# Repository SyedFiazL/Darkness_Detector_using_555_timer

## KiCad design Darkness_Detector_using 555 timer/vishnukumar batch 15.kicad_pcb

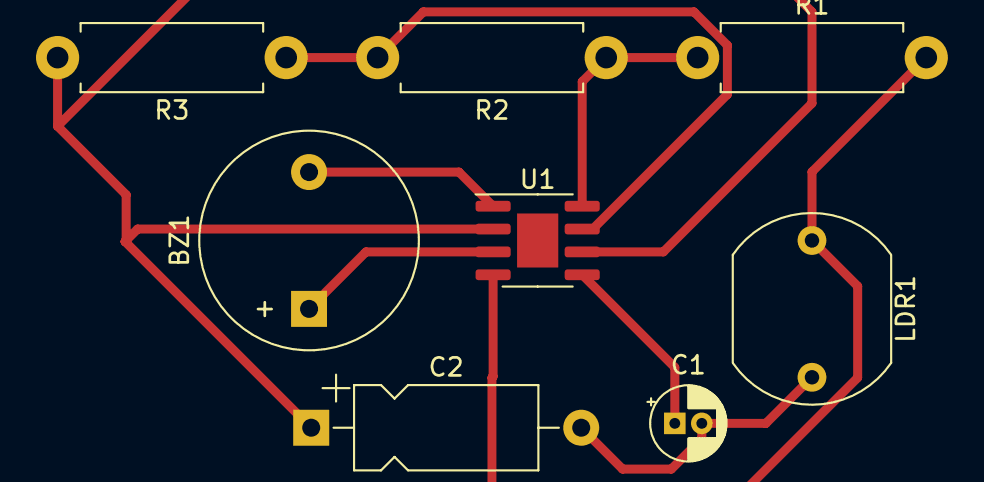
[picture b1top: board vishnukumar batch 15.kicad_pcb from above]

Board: 2 copper layers, 8 parts (0 on the bottom side), 8 nets.

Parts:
BZ1: Buzzer; Buzzer_12x9.5RM7.6
C1: 0.1nF; CP_Radial_D4.0mm_P1.50mm
C2: 1uF; CP_Axial_L10.0mm_D4.5mm_P15.00mm_Horizontal
LDR1: LDR; R_LDR_10x8.5mm_P7.6mm_Vertical
R1: 1M; R_Axial_DIN0411_L9.9mm_D3.6mm_P12.70mm_Horizontal
R2: 2.2k; R_Axial_DIN0411_L9.9mm_D3.6mm_P12.70mm_Horizontal
R3: 10k; R_Axial_DIN0411_L9.9mm_D3.6mm_P12.70mm_Horizontal
U1: LM555xM; SOIC-8-1EP_3.9x4.9mm_P1.27mm_EP2.29x3mm

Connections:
GND: BZ1.2 (+), U1.1 (GND)
unnamed: BZ1.1 (-), U1.3 (Q)
unnamed: C1.1, U1.5 (CV)
unnamed: C1.2, C2.2, LDR1.2
unnamed: C2.1, R3.2, U1.2 (TR), U1.6 (THR)
unnamed: LDR1.1, R1.2, U1.4 (R)
unnamed: R2.2, R3.1, U1.7 (DIS)
VCC: R1.1, R2.1, U1.8 (VCC)
